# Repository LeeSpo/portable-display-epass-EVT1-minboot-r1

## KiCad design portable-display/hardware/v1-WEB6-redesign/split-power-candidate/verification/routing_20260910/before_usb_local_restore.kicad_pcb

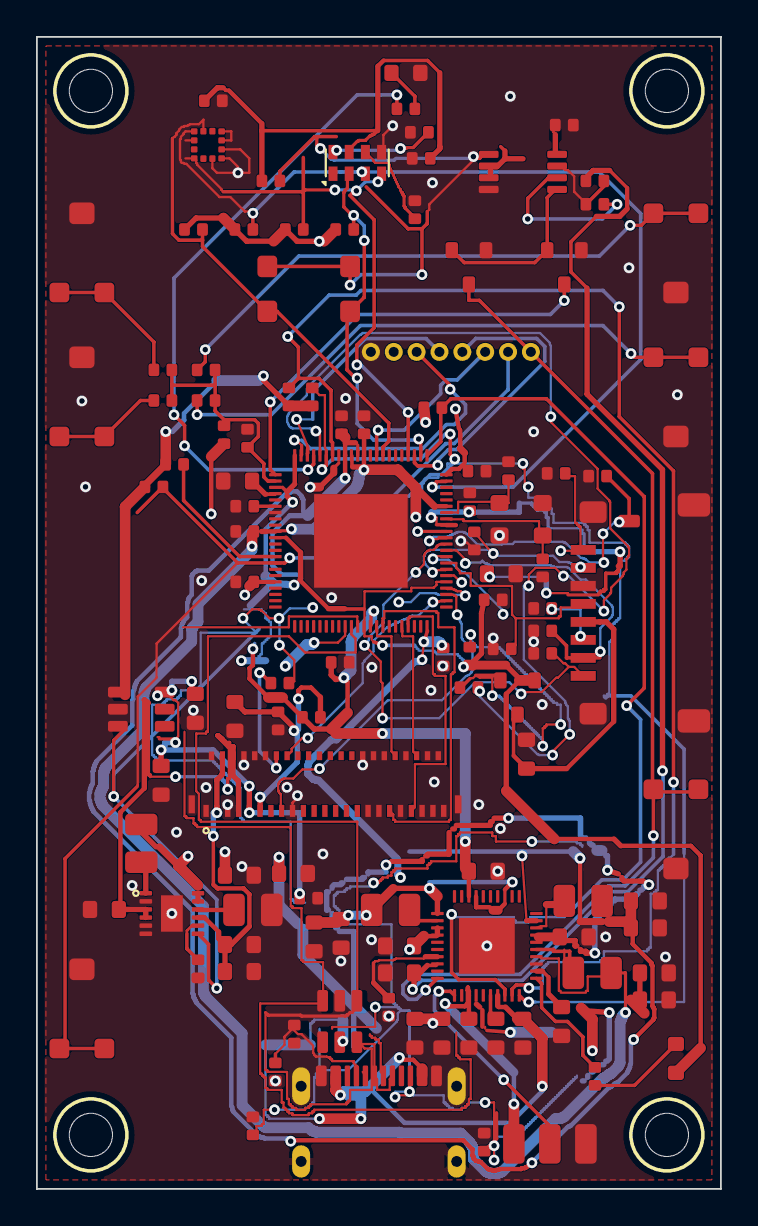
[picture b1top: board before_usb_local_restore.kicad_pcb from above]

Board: 4 copper layers, 38.0 x 64.0 mm, 119 parts (0 on the bottom side), 80 nets.

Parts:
C1, C2, C4, C5, C6, C7, C8, C9: 22u; 0603
C3, C11, C33, C40, C41, C42, C44: 1u; 0603
C10, C34, C35, C38: 2.2u; 0603
C12, C13: 18p; 0402
C14, C15, C16, C17, C18, C19, C20, C21, C23, C24, C25, C26, C37, C39, C43, C45, C51: 100n; 0402
C29: 4.7u; 0603
C30, C32, C46, C47, C48, C49, C50: 10u; 0603
C31: 10n; 0402
C36: 470n; 0402
D1: CHARGE; LED0603
D2, D3: BAT54; D_SOD123
D5: STATUS; LED0603
D6, D7, D8, D9, D10, D11, D12, D13, D14: PESD4V0; 0402
H1: M2; MountingHole_1
H2: M2; MountingHole_2
H3: M2; MountingHole_3
H4: M2; MountingHole_4
J1: USB4105-GF-A-060; USB4105
J2: 1S LiPo + NTC; BAT3
J3: DEBUG POGO; HDR8
J4: KD024EGOIN152-01; FPC45
J5: MicroSD; MICROSD
L1, L2, L3: 1uH/2A; IND_2x2
L5, L6: 4.7uH; IND_2x2
Q1, Q2: 2N7002; SOT23-3
Q3: AO3401A; SOT23-3
R1, R2: 5.1k; 0402
R3, R15, R16: 4.7k; 0402
R4, R5, R6, R27: 2.2k; 0402
R10, R11, R13, R14, R17, R18, R21, R28: 10k; 0402
R12: 820k; 0402
R20, R22, R26: 100k; 0402
R23, R29, R31: 0R; 0402
R24: 22k; 0402
R25: 47k; 0402
SW1: UP; SW_SIDE
SW2: DOWN; SW_SIDE
SW3: OK; SW_SIDE
SW4: BACK; SW_SIDE
SW5: POWER; SW_SIDE
SW6: FEL; SW_SIDE
U1: AXP2101; QFN40
U2: V851s; QFN88
U4: LIS2DW12TR; LGA-12
U5: RV-3028-C7; RTC-8
U6: SN74LVC1G123DCTR; SN74LVC1G123_DCT8
U8: TPS22918DBVR; TPS22918_DBV6
U9: USBLC6-2SC6; USBLC6-2SC6_SOT23-6
U10: TPS65631DPDR; WSON-12
Y1: 24MHz 10ppm; XTAL4

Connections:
1V8: C10.1, C16.1, C17.1, R22.1, R29.1, U1.18 (ALDO1), U2.37 (VDD18_DRAM), U2.62 (VCC_PA_MCSI), U2.79 (VCC18_MDSI)
3V3: C4.1, C5.1, C14.1, C15.1, D1.1, J3.2 (3V3), L1.2, Q3.2 (S), R3.1, R4.1, R5.1, R10.1, R15.1, R16.1, R17.1, R18.1, R20.1, R28.1, U1.13 (BLDOIN), U1.17 (ALDOIN), U1.21 (FB1), U2.5 (VCC33_PF_PD), U2.22 (VCC_PE), U2.44 (VCC_IO), U2.47 (VDD33), U2.55 (VCC_PC), U2.78 (VCC33_USB), U8.1 (VIN)
ACCEL_INT_N: D3.1, R18.2, U2.30 (PE6), U4.12 (INT1)
ADC_KEYS: C31.1, R22.2, R23.2, R24.2, R25.2, R26.2, U2.46 (GPADC0)
BAT_NTC: J2.2 (NTC), U1.31 (TS)
BOOT0: J3.7 (FEL_PC2), R10.2, SW6.1 (FEL_PC2), SW6.2 (FEL_PC2), U2.59 (PC2_SPI0_MOSI_BOOT0)
BOOT1: R28.2, U2.58 (PC3_SPI0_MISO_BOOT1)
CHGLED_A: D1.2, R6.1
CHGLED_N: R6.2, U1.1 (CHGLED)
CORE_0V93: C6.1, C7.1, C18.1, C19.1, C20.1, L2.2, U1.4 (FB3), U2.13 (VDD_SYS0), U2.17 (VDD_SYS1), U2.33 (VDD_SYS2), U2.35 (VDD_SYS3), U2.54 (VDD_SYS4), U2.75 (VDD_SYS5), U2.88 (VDD_SYS6)
DRAM_1V5: C8.1, C9.1, C21.1, L3.2, U1.9 (FB4), U2.34 (VCC_DRAM0), U2.36 (VCC_DRAM1)
DSI_CKN: J4.40 (CLKN), U2.84 (PD5_DSI_CKN)
DSI_CKP: J4.39 (CLKP), U2.85 (PD6_DSI_CKP)
DSI_D0N: J4.36 (D0N), U2.80 (PD1_DSI_D0N)
DSI_D0P: J4.35 (D0P), U2.81 (PD2_DSI_D0P)
E907_RX: J3.6 (E907_RX), U2.31 (PE1)
E907_TX: J3.5 (E907_TX), U2.25 (PE0)
ELVDD: C48.1, J4.6 (ELVDD), J4.7 (ELVDD), U10.3 (OUTP), U10.4 (FBS)
ELVSS: C49.1, C50.1, J4.3 (ELVSS), J4.4 (ELVSS), U10.9 (OUTN)
EL_CT: C51.1, U10.8 (CT)
EL_SWN: L6.1, U10.10 (SWN)
EL_SWP: L5.2, U10.1 (SWP)
GND: C1.2, C2.2, C3.2, C4.2, C5.2, C6.2, C7.2, C8.2, C9.2, C10.2, C11.2, C12.2, C13.2, C14.2, C15.2, C16.2, C17.2, C18.2, C19.2, C20.2, C21.2, C24.2, C25.2, C26.2, C29.2, C30.2, C31.2, C32.2, C33.2, C34.2, C35.2, C36.2, C37.2, C38.2, C39.2, C40.2, C41.2, C42.2, C43.2, C44.2, C45.2, C46.2, C47.2, C48.2, C49.2, C50.2, C51.2, D5.2, D6.2, D7.2, D8.2, D9.2, D10.2, D11.2, D12.2, D13.2, D14.2, J1.A1 (GND), J1.A12 (GND), J1.B1 (GND), J1.B12 (GND), J1.SH1 (SHIELD), J1.SH2 (SHIELD), J1.SH3 (SHIELD), J1.SH4 (SHIELD), J2.3 (GND), J3.1 (GND), J4.1 (GND), J4.2 (GND), J4.5 (GND), J4.8 (GND), J4.10 (GND), J4.12 (GND), J4.17 (GND), J4.30 (GND), J4.31 (IM1), J4.32 (IM0), J4.33 (GND), J4.34 (GND), J4.37 (GND), J4.38 (GND), J4.41 (GND), J4.42 (GND), J4.43 (MTP), J4.44 (GND), J4.45 (GND), J4.MP1 (MOUNT), J4.MP2 (MOUNT), J5.6 (VSS), J5.10 (SH), J5.11 (SH), J5.12 (SH), J5.13 (SH), L6.2, Q1.2 (S), Q2.2 (S), R1.2, R2.2, R13.2, R14.2, SW1.3 (GND), SW2.3 (GND), SW3.3 (GND), SW4.3 (GND), SW5.3 (GND), SW6.3 (GND), U1.3 (GND), U1.41 (EPAD), U2.51 (AGND), U2.89 (EPAD), U4.6 (GND), U4.7 (RES), U4.8 (GND), U5.5 (VSS), U6.4 (GND), U8.2 (GND), U9.2 (GND), U10.2 (PGND), U10.5 (AGND), U10.6 (GND), U10.13 (EPAD), Y1.2 (GND), Y1.4 (GND)
I2C0_SCL: R15.2, U2.21 (PE4), U4.1 (SCL), U5.3 (SCL)
I2C0_SDA: R16.2, U2.26 (PE5), U4.4 (SDA), U5.4 (SDA)
KEY_BACK: R26.1, SW4.1 (KEY), SW4.2 (KEY)
KEY_DOWN: R24.1, SW2.1 (KEY), SW2.2 (KEY)
KEY_OK: R25.1, SW3.1 (KEY), SW3.2 (KEY)
KEY_UP: R23.1, SW1.1 (KEY), SW1.2 (KEY)
LCD_1V8: C44.1, C45.1, J4.11 (VDDIO), R29.2
LCD_3V3: C29.1, C42.1, C43.1, J4.9 (VCI), U8.6 (VOUT)
LCD_EN: R31.2, U2.4 (PD21), U8.3 (ON), U10.7 (CTRL)
LCD_RST: J4.16 (RESX), U2.2 (PD19)
LCD_SWIRE: J4.14 (SWIRE), R31.1
LCD_TE: J4.15 (TE), U2.3 (PD20)
LX_3V3: L1.1, U1.22 (LX1)
LX_CORE: L2.1, U1.5 (LX3)
LX_DRAM: L3.1, U1.8 (LX4)
PMIC_BACKUP: C39.1, U1.27 (VBACKUP)
PMIC_IRQ_N: R3.2, U1.38 (IRQ), U2.23 (PE2)
PMIC_SCL: R4.2, U1.40 (SCK), U2.39 (PH13)
PMIC_SDA: R5.2, U1.39 (SDA), U2.38 (PH14)
PWRON_N: J3.8 (PWRON_N), Q1.3 (D), SW5.1 (PWRON), SW5.2 (PWRON), U1.30 (PWRON)
RTC_3V3: C24.1, C25.1, C26.1, C33.1, R11.1, R12.1, U1.28 (VRTC), U4.2 (CS), U4.9 (VDD), U4.10 (VDDIO), U5.7 (VDD), U6.2 (B), U6.3 (/CLR), U6.8 (VCC)
RTC_EVI: R14.1, U5.8 (EVI)
RTC_INT_N: D2.1, R17.2, U2.24 (PE7), U5.2 (INT)
RTC_VBACKUP: R13.1, U5.6 (VBACKUP)
SD_3V3: C30.1, J5.4 (VDD), Q3.3 (D)
SD_CLK: D9.1, J5.5 (CLK), U2.8 (PF2_SDC0_CLK)
SD_CMD: D8.1, J5.3 (CMD), U2.9 (PF3_SDC0_CMD)
SD_D0: D10.1, J5.7 (DAT0), U2.7 (PF1_SDC0_D0)
SD_D1: D11.1, J5.8 (DAT1), U2.6 (PF0_SDC0_D1)
SD_D2: D6.1, J5.1 (DAT2), U2.11 (PF5_SDC0_D2)
SD_D3: D7.1, J5.2 (DAT3), U2.10 (PF4_SDC0_D3)
SD_DET: D12.1, J5.9 (CD), U2.12 (PF6_DBG_CLK)
SD_PWR_EN: R21.1, U2.40 (PH12)
SD_PWR_GATE: Q3.1 (G), R20.2, R21.2
SOC_AVCC: C35.1, U2.48 (AVCC)
SOC_LDO_1V8: C34.1, C37.1, U2.14 (VCC_LDOA_PLL)
STATUS_LED: R27.1, U2.41 (PH11)
STATUS_LED_A: D5.1, R27.2
UART0_RX: J3.4 (UART0_RX), U2.42 (PH10)
UART0_TX: J3.3 (UART0_TX), U2.43 (PH9)
USB_CC1: D13.1, J1.A5 (CC1), R1.1
USB_CC2: D14.1, J1.B5 (CC2), R2.1
USB_DM: J1.A7 (DM1), J1.B7 (DM2), U2.77 (USB0_DM), U9.3 (I/O2), U9.4 (I/O2)
USB_DP: J1.A6 (DP1), J1.B6 (DP2), U2.76 (USB0_DP), U9.1 (I/O1), U9.6 (I/O1)
VBAT: C3.1, J2.1 (VBAT), U1.33 (BAT)
VBUS: C32.1, J1.A4 (VBUS), J1.A9 (VBUS), J1.B4 (VBUS), J1.B9 (VBUS), U1.37 (VBUS), U9.5 (VBUS)
VMID: C38.1, U1.36 (VMID)
VRA1: C36.1, U2.50 (VRA1)
VREF: C11.1, U1.2 (VREF)
VSYS: C1.1, C2.1, C40.1, C41.1, C46.1, C47.1, L5.1, U1.6 (VIN3), U1.7 (VIN4), U1.23 (VIN1), U1.24 (VIN2), U1.34 (VSYS), U10.11 (AVIN), U10.12 (PVIN)
WAKE_CEXT: C23.2, U6.6 (CEXT)
WAKE_PULSE: Q1.1 (G), Q2.1 (G), U6.5 (Q)
WAKE_PULSE_N: Q2.3 (D), U2.45 (PH0)
WAKE_REQ_N: D2.2, D3.2, R11.2, U6.1 (/A)
WAKE_REXT: C23.1, R12.2, U6.7 (REXT_CEXT)
XIN: C12.1, U2.16 (DXIN), Y1.1 (XIN)
XOUT: C13.1, U2.15 (DXOUT), Y1.3 (XOUT)

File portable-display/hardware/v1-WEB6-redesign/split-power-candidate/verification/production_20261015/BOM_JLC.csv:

Comment,Designator,Footprint,LCSC Part #,Quantity
22u,"C1,C2",0603,C86295,2
1u,"C3,C11,C33,C40,C41,C42,C44",0603,C15849,7
22u,"C4,C5,C6,C7,C8,C9",0603,C59461,6
2.2u,"C10,C35,C38",0603,C23630,3
18p,"C12,C13",0402,C1549,2
100n,"C14,C15,C16,C17,C18,C19,C20,C21,C24,C25,C26,C37,C39,C43,C45,C51,C52,C54,C57,C59,C60,C62",0402,C1525,22
3.3u,C23,C_0805_2012Metric,C7393948,1
4.7u,C29,0603,C19666,1
10u,"C30,C32,C48,C49,C50",0603,C19702,5
10n,C31,0402,C15195,1
2.2u,C34,0402,C12530,1
470n,C36,0402,C47339,1
10u,"C46,C47",0402,C15525,2
1u,C53,0402,C52923,1
CHARGE,D1,LED0603,C12624,1
BAT54,"D2,D3",D_SOD123,C699107,2
STATUS,D5,LED0603,C2288,1
ESDLC5V0LB,"D13,D14",DFN1006-2,C20168172,2
USB4105-GF-A-060,J1,USB4105,C3025063,1
1S LiPo + NTC,J2,SH1.0_3P_RA,C7430445,1
KD024EGOIN152-01,J4,FPC45,C5365339,1
MicroSD,J5,XKTF-0803-0,C381083,1
1uH/2A,"L1,L2,L3",IND_2x2,C97002,3
4.7uH,"L5,L6",IND_2x2,C97018,2
2N7002,"Q1,Q2",SOT23-3,C8545,2
AO3401A,Q3,SOT23-3,C15127,1
5.1k,"R1,R2",0402,C25905,2
4.7k,"R3,R15,R16",0402,C25900,3
2.2k,"R4,R5,R6,R27",0402,C25879,4
10k,"R10,R11,R13,R14,R17,R18,R20,R28,R32,R34,R35",0402,C25744,11
910k,R12,0402,C352384,1
100,R21,0402,C25076,1
100k,"R22,R26",0402,C25741,2
0R,"R23,R29,R36,R37,R38,R39,R40",0402,C17168,7
22k,R24,0402,C25768,1
47k,R25,0402,C25792,1
1k,R33,0402,C11702,1
UP,SW1,SW_SIDE,C5117859,1
DOWN,SW2,SW_SIDE,C5117859,1
OK,SW3,SW_SIDE,C5117859,1
BACK,SW4,SW_SIDE,C5117859,1
POWER,SW5,SW_SIDE,C5117859,1
FEL,SW6,SW_SIDE,C5117859,1
AXP2101,U1,QFN40,C3036461,1
V851s,U2,QFN88,C5365286,1
LIS2DW12TR,U4,LGA-12,C189624,1
RV-3028-C7,U5,RTC-8,C3019759,1
SN74LVC1G123DCTR,U6,SN74LVC1G123_DCT8,C123302,1
TPS22918DBVR,U8,TPS22918_DBV6,C131941,1
USBLC6-2SC6,U9,USBLC6-2SC6_SOT23-6,C2827654,1
TPS65631DPDR,U10,WSON-12,C165127,1
SN74LVC2G17DBVR,U11,SN74LVC2G17_DBV6,C10429,1
TPD4E05U06DQAR,"U12,U13",TPD4E05U06_DQA,C138714,2
24MHz 10ppm,Y1,XTAL4,C16197264,1
